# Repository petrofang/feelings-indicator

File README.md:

# feelings-indicator
EAGLE CAD schematics and boards for the Feelings Indicator line of products

Feelings Indicator is a simple circuit and demostation of how to use Eagle
CAD and how to get printed circuit board (PCB) designs fabricated cheaply
and easily. 

As a functional product it can work as a communication tool for those with
limited communication skill or capacity. It is also an enjoyable fidget toy.

Included Files:

main.brd   . . . . . . . . . . . . . EAGLE CAD board file

main.sch   . . . . . . . . . . . . . EAGLE CAD schematic

main.pdf   . . . . . . . . . . . . . PDF schematic

main_oshpark-top.png   . . . . . . . OSH Park render

main_oshpark-bottom.png  . . . . . . OSH Park render

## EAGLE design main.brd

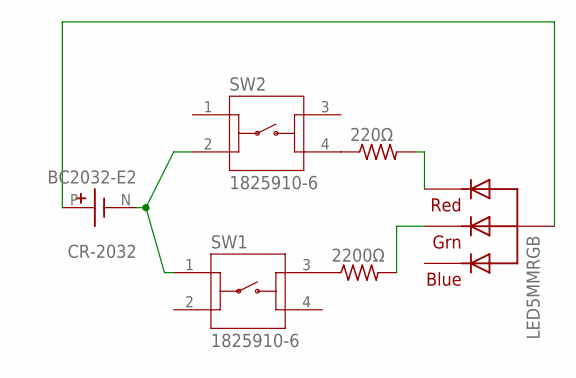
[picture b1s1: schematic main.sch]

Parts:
220Ω, 2200Ω: R-US_0204/5; 0204/5
CR-2032: BC2032-E2; MPD_BC2032-E2
LED5MMRGB: RGBLED_CA-5MM; LED5MMRGB
SW1, SW2: 1825910-6; SW_1825910-6-4

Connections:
unnamed: CR-2032.N, SW1.1, SW2.2
unnamed: 2200Ω.1, SW1.3
unnamed: 220Ω.1, SW2.4
unnamed: 2200Ω.2, LED5MMRGB.3 (GREEN)
unnamed: 220Ω.2, LED5MMRGB.1 (RED)
unnamed: CR-2032.P, LED5MMRGB.2 (VCC)

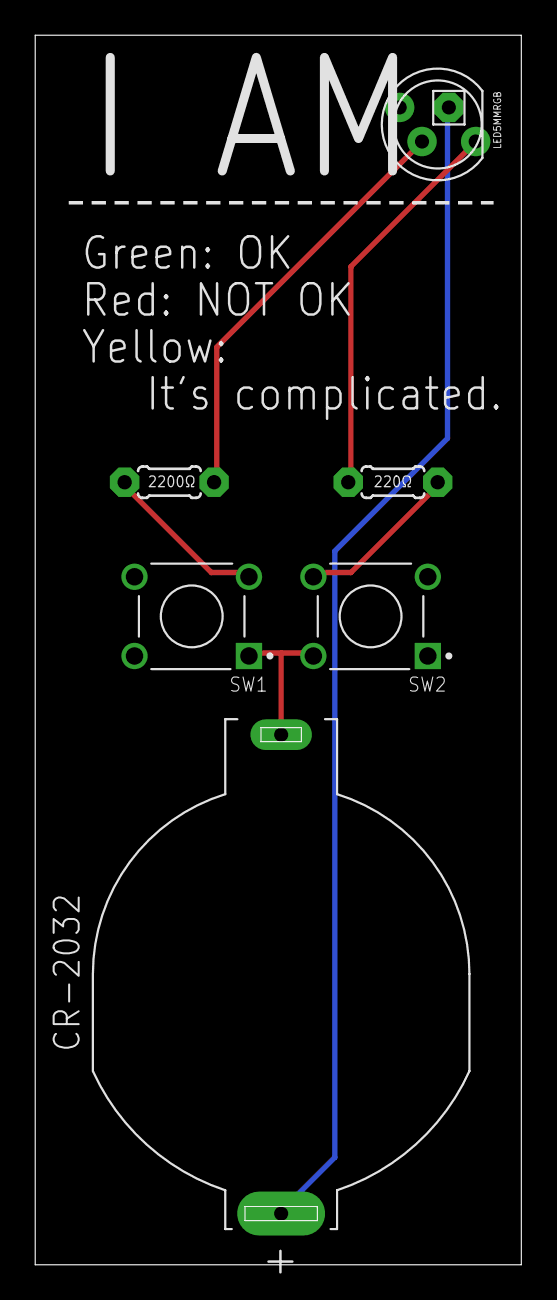
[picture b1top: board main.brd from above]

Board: 2 copper layers, 27.6 x 69.8 mm, 6 parts (0 on the bottom side), 6 nets.

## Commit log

2019-02-17 first commit.
2019-02-17 Added PNGs of OSH Park Mockups
2019-02-17 Refactored autorouting with new net class and did DRC
2019-02-17 Updated PNGs from OSH Park
2019-02-17 README.md
